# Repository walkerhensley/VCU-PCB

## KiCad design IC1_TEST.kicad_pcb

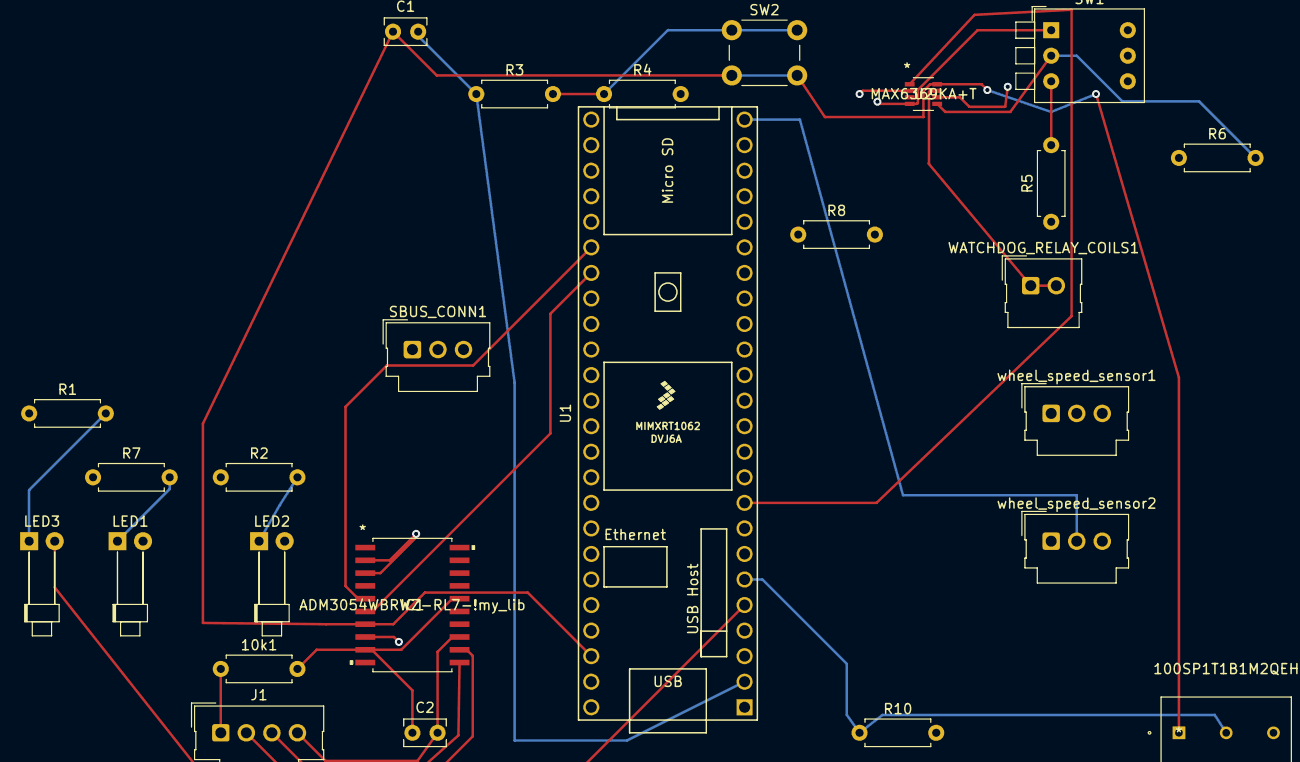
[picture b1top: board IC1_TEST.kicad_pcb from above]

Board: 4 copper layers, 26 parts (0 on the bottom side), 27 nets.

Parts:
10k1: 10000; R_Axial_DIN0207_L6.3mm_D2.5mm_P7.62mm_Horizontal
C1: C_Small; C_Rect_L4.0mm_W2.5mm_P2.50mm
C2: 0.1e-6; C_Rect_L4.0mm_W2.5mm_P2.50mm
IC1: ADM3054WBRWZ-RL7-!my_lib; ADM3053BRWZ
J1: B4B-XH-A_LF__SN_-!my_lib; Molex_SL_171971-0004_1x04_P2.54mm_Vertical
LED1, LED2, LED3: LED; LED_D1.8mm_W1.8mm_H2.4mm_Horizontal_O6.35mm_Z4.9mm
R1, R2, R7: 220; R_Axial_DIN0207_L6.3mm_D2.5mm_P7.62mm_Horizontal
R3: 10K; R_Axial_DIN0207_L6.3mm_D2.5mm_P7.62mm_Horizontal
R4: 100K; R_Axial_DIN0207_L6.3mm_D2.5mm_P7.62mm_Horizontal
R5, R6, R8: R_US; R_Axial_DIN0207_L6.3mm_D2.5mm_P7.62mm_Horizontal
R10: 10000; R_Axial_DIN0207_L6.3mm_D2.5mm_P7.62mm_Horizontal
SBUS_CONN1: Conn_01x03_Female; Molex_SL_171971-0003_1x03_P2.54mm_Vertical
SW1: SW_DIP_x03; SW_DIP_SPSTx03_Piano_10.8x9.18mm_W7.62mm_P2.54mm
SW2: SW_Push; SW_PUSH_6mm_H4.3mm
U1: DEV-16771; Teensy41
U2: MAX6369KA+T; MAX6369KA&plus_T
WATCHDOG_RELAY_COILS1: Conn_01x02_Female; Molex_SL_171971-0002_1x02_P2.54mm_Vertical
reset_switch1: 100SP1T1B1M2QEH
wheel_speed_sensor1, wheel_speed_sensor2: Conn_01x03_Female; Molex_SL_171971-0003_1x03_P2.54mm_Vertical

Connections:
3.3v_SUPPLY: C1.1, IC1.7 (VDD1), SW2.2, U1.3.3v_SUPPLY, U2.8 (VCC), reset_switch1.1
+5V: R5.1, R6.1, R8.1, SBUS_CONN1.2, U1.VIN, wheel_speed_sensor1.1, wheel_speed_sensor2.1
CAN_H: IC1.12 (CANH), J1.2
CAN_L: IC1.11 (CANL), J1.3
CRX: IC1.5 (RXD), U1.30 (CRX3)
CTX: IC1.6 (TXD), U1.31 (CTX3)
DIO_BUTTON: R10.1, U1.6 (OUT1D), reset_switch1.2
DIO_SWITCH: C1.2, R3.1, U1.2 (OUT2)
DIO_WATCHDOG: U1.9 (OUT1C), U2.1 (WDI)
GNDREF: IC1.2 (GND1_1), IC1.3 (GND1_2), IC1.8 (GND1_3), R1.1, R2.1, R4.2, R7.1, R10.2, SBUS_CONN1.1, SW1.4, SW1.5, SW1.6, U1.GND, U2.2 (GND), wheel_speed_sensor1.3, wheel_speed_sensor2.3
LED1: LED1.2 (A), U1.3 (LRCLK2)
LED2: LED2.2 (A), U1.4 (BCLK2)
LED3: LED3.2 (A), U1.5 (IN2)
unnamed: 10k1.1, J1.1
unnamed: LED1.1 (K), R7.2
unnamed: LED2.1 (K), R2.2
unnamed: LED3.1 (K), R1.2
unnamed: R3.2, R4.1, SW2.1
ODRIVE_5V+: C2.2, IC1.13 (VDD2), J1.4
ODRIVE_GND: 10k1.2, C2.1, IC1.9 (GND2_1), IC1.16 (GND2_2)
SBUS: SBUS_CONN1.3, U1.34 (RX8)
SET0: R8.2, SW1.1, U2.4 (SET0)
SET1: R6.2, SW1.2, U2.5 (SET1)
SET2: R5.2, SW1.3, U2.6 (SET2)
WATCHDOG_OUTPUT: U1.17 (A3), U2.7 (*WDO), WATCHDOG_RELAY_COILS1.1, WATCHDOG_RELAY_COILS1.2
wheel_speed_sensor1: U1.25 (A11), wheel_speed_sensor1.2
wheel_speed_sensor2: U1.24 (A10), wheel_speed_sensor2.2

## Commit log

2022-02-28 pcb changes
    changed connectors, redid wire paths
2022-02-28 pcb changes
    moved R5, redid wire routing
2022-02-28 connected to gndref on chips
2022-02-28 no more overlapping w/ pads, finished teensy pins
2022-02-28 wiring changes
2022-02-28 added watchdog output connection to teensy

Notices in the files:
parts and their libraries:
Copyright 2021 Accelerated Designs. All rights reserved.
